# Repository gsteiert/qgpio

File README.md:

# qgpio
Qwiic GPIO expander

This is a PCF8574 based GPIO expander with Qwiic connectors.
Each GPIO and the INT signal go to a header pin and have and LED that indicates when the signal is low.  The signals go to a dual row header with one row grounded so that any signal can be shorted with a jumper.  There is also an LED to indicate when the board is powered. 

This design is released under CC0 1.0 Universal license.

[Schematic print](qgpio.pdf)

[Follow this project on Hackaday](https://hackaday.io/project/173648-qgpio)

You can [order bare boards from OSH Park](https://oshpark.com/shared_projects/7lsaSVpY)

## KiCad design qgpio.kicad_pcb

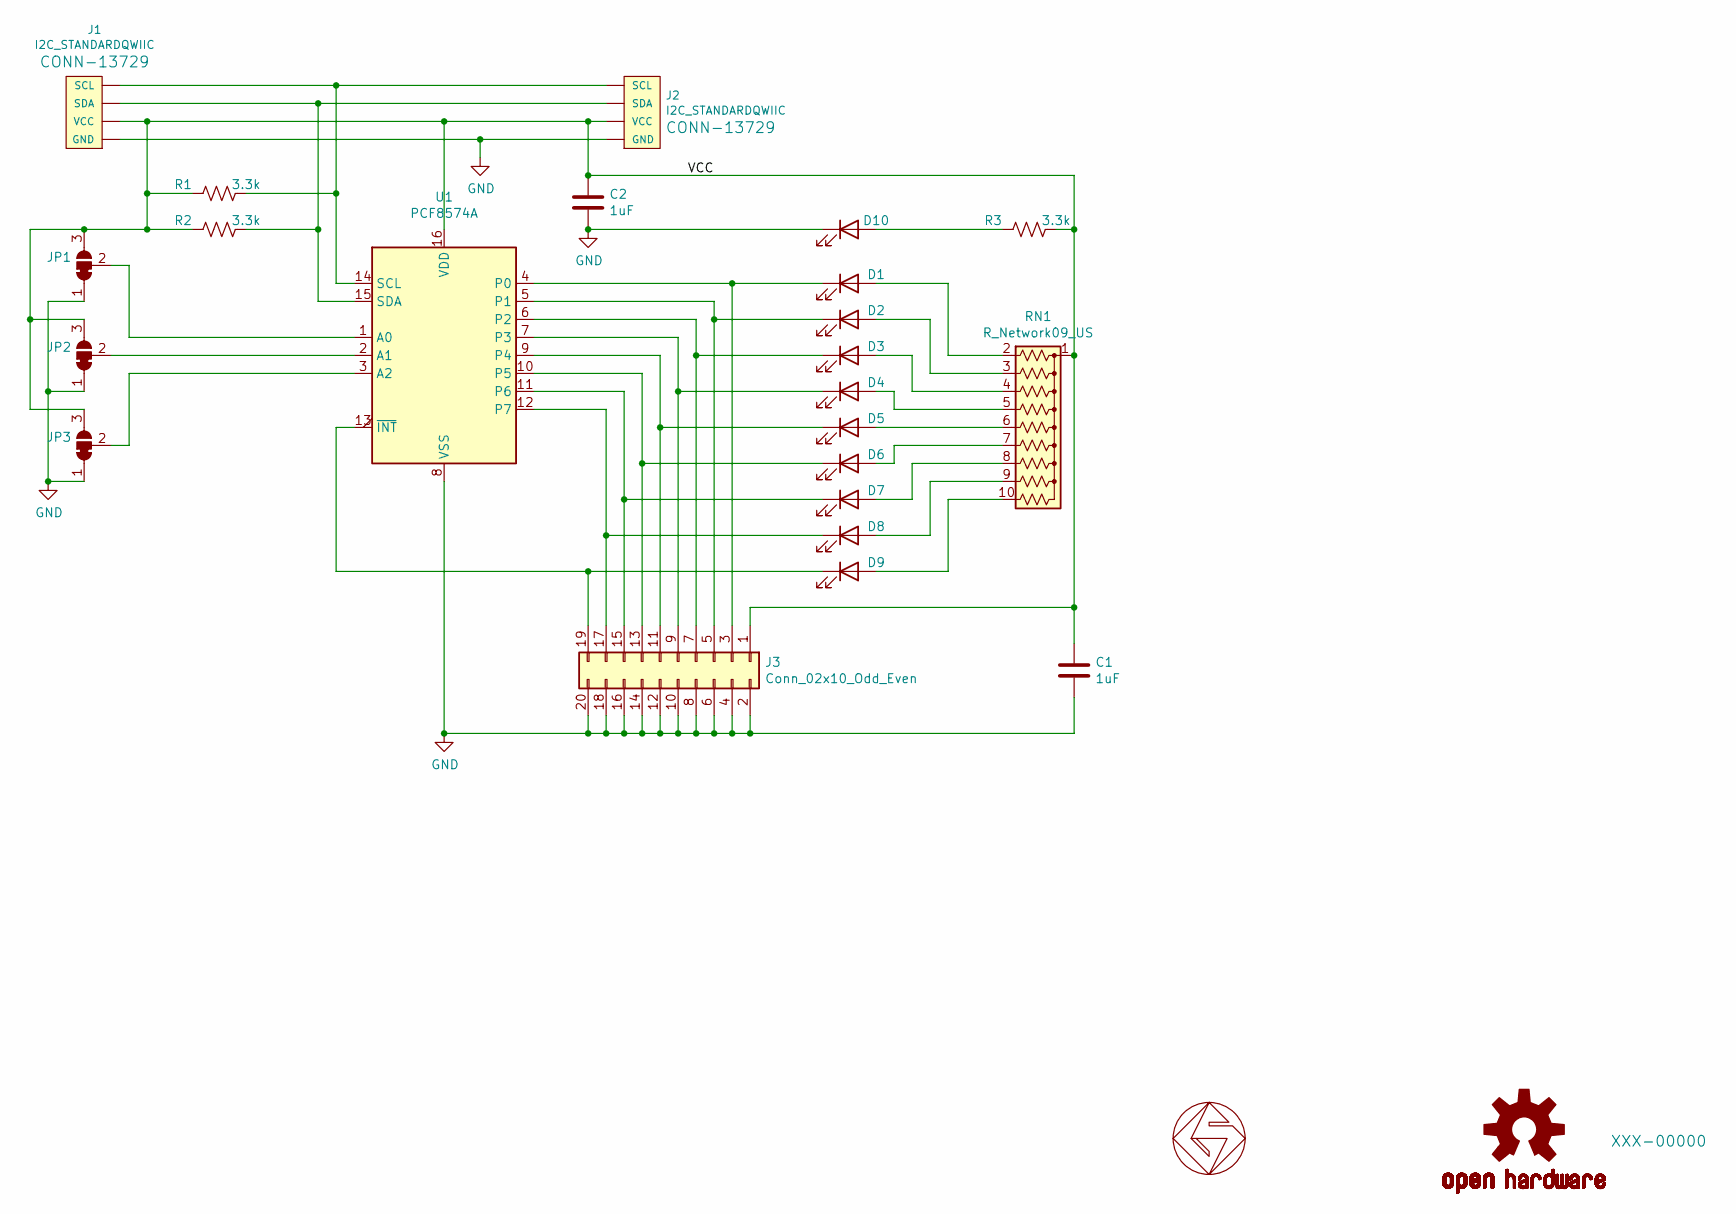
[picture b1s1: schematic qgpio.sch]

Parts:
C1, C2: 1uF; C0603
D1, D2, D3, D4, D5, D6, D7, D8, D9, D10: LED; LED_0603_1608Metric
GS1: GS_logo; gs_logo_200mil
J1, J2: I2C_STANDARDQWIIC; JST_SH_SM04B-SRSS-TB_1x04-1MP_P1.00mm_Horizontal
J3: Conn_02x10_Odd_Even; PinHeader_2x10_P2.54mm_Vertical
JP1, JP2, JP3: SolderJumper_3_Bridged12; SolderJumper-3_P1.3mm_Bridged12_RoundedPad1.0x1.5mm
LOGO1: OSHW-LOGOS; OSHW-Logo2_7.3x6mm_SilkScreen
R1, R2, R3: 3.3k; C0603
RN1: R_Network09_US; R_Array_SIP10
U1: PCF8574A; SOIC-16W_7.5x10.3mm_P1.27mm

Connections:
/VCC: C1.1, C2.1, J1.2 (VCC), J2.2 (VCC), J3.1, JP1.3 (B), JP2.3 (B), JP3.3 (B), R1.2, R2.2, R3.1, RN1.1 (common), U1.16 (VDD)
GND: C1.2, C2.2, D10.1 (K), J1.1 (GND), J2.1 (GND), J3.2, J3.4, J3.6, J3.8, J3.10, J3.12, J3.14, J3.16, J3.18, J3.20, JP1.1 (A), JP2.1 (A), JP3.1 (A), U1.8 (VSS)
unnamed: D1.1 (K), J3.3, U1.4 (P0)
unnamed: D1.2 (A), RN1.2 (R1)
unnamed: D2.1 (K), J3.5, U1.5 (P1)
unnamed: D2.2 (A), RN1.3 (R2)
unnamed: D3.1 (K), J3.7, U1.6 (P2)
unnamed: D3.2 (A), RN1.4 (R3)
unnamed: D4.1 (K), J3.9, U1.7 (P3)
unnamed: D4.2 (A), RN1.5 (R4)
unnamed: D5.1 (K), J3.11, U1.9 (P4)
unnamed: D5.2 (A), RN1.6 (R5)
unnamed: D6.1 (K), J3.13, U1.10 (P5)
unnamed: D6.2 (A), RN1.7 (R6)
unnamed: D7.1 (K), J3.15, U1.11 (P6)
unnamed: D7.2 (A), RN1.8 (R7)
unnamed: D8.1 (K), J3.17, U1.12 (P7)
unnamed: D8.2 (A), RN1.9 (R8)
unnamed: D9.1 (K), J3.19, U1.13 (~INT~)
unnamed: D9.2 (A), RN1.10 (R9)
unnamed: D10.2 (A), R3.2
unnamed: J1.3 (SDA), J2.3 (SDA), R2.1, U1.15 (SDA)
unnamed: J1.4 (SCL), J2.4 (SCL), R1.1, U1.14 (SCL)
unnamed: JP1.2 (C), U1.1 (A0)
unnamed: JP2.2 (C), U1.2 (A1)
unnamed: JP3.2 (C), U1.3 (A2)

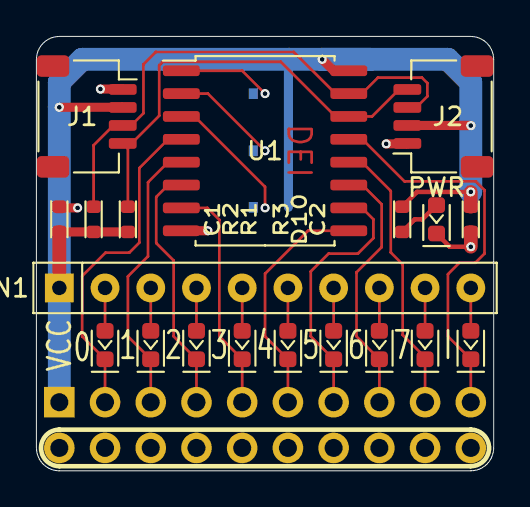
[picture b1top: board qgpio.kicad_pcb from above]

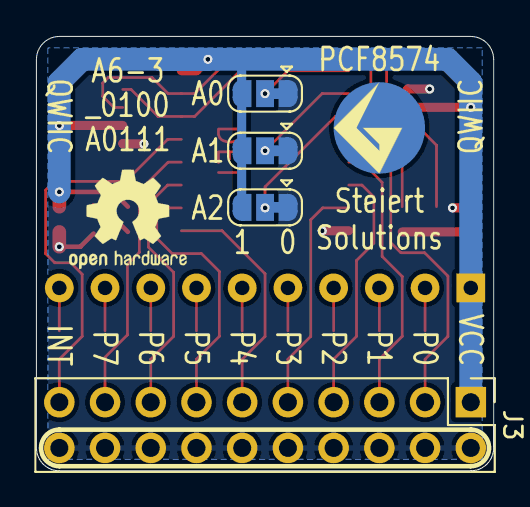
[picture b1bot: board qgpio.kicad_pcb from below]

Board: 2 copper layers, 25.4 x 24.1 mm, 25 parts (6 on the bottom side), 26 nets.

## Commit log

2020-06-26 added images
2020-06-27 changed ground silkscreen on dual row header
2020-06-27 exported sch to pdf
2020-07-07 added I2C addr to back silk
2020-07-09 cleaned up BOM
2020-07-09 added 3d views
2020-07-09 updated images
2020-07-09 Update README.md
    updated flow
2020-07-17 added CC0 license
2020-07-29 Adding OSHWA certification mark
2020-07-29 Added OSHWA Mark
